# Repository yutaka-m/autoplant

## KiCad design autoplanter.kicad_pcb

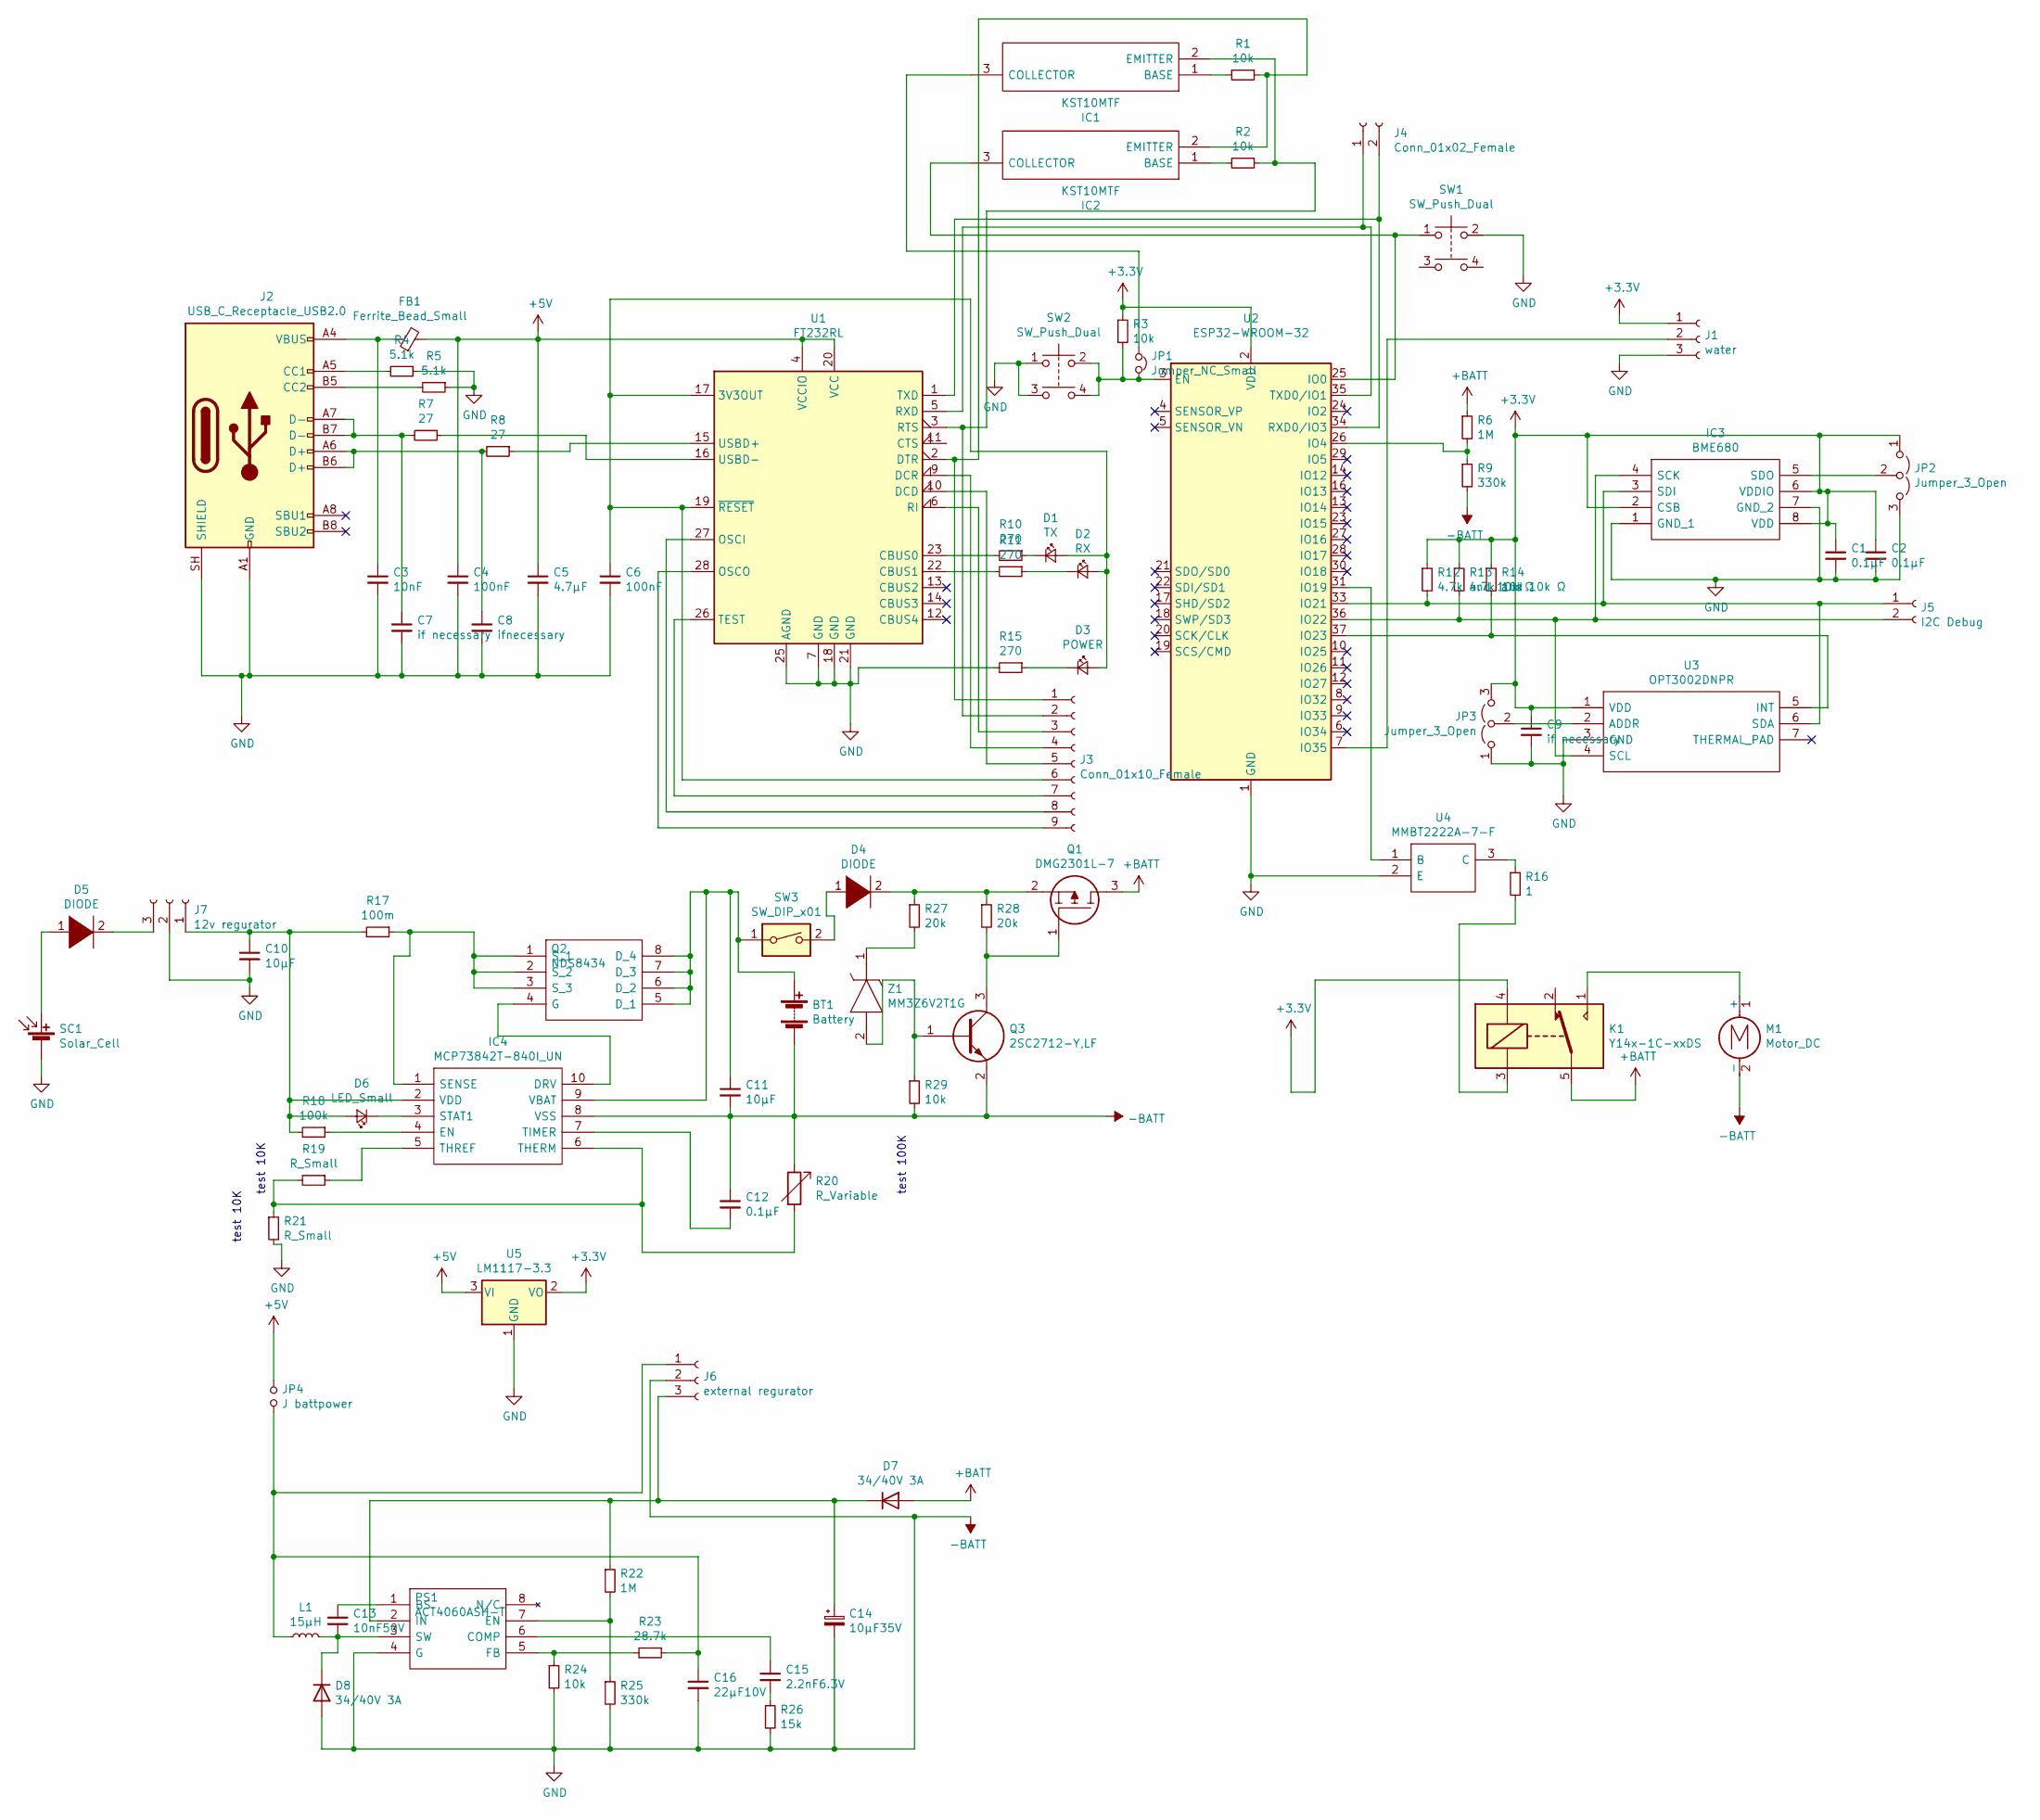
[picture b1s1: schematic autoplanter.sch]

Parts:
BT1: Battery; PinSocket_1x02_P2.54mm_Vertical
C1, C2, C12: 0.1μF; C_1206_3216Metric
C3: 10nF; C_1206_3216Metric
C4, C6: 100nF; C_1206_3216Metric
C5: 4.7μF; C_1206_3216Metric
C7, C9: if necessary; C_1206_3216Metric
C8: ifnecessary; C_1206_3216Metric
C10, C11: 10μF; C_1206_3216Metric
C13: 10nF50V; C_1206_3216Metric
C14: 10μF35V; C_1206_3216Metric
C15: 2.2nF6.3V; C_1206_3216Metric
C16: 22μF10V; C_1206_3216Metric
D1: TX; C_1206_3216Metric
D2: RX; C_1206_3216Metric
D3: POWER; C_1206_3216Metric
D4, D5: DIODE; DIONM7959X282N
D6: LED_Small; C_1206_3216Metric
D7, D8: 34/40V 3A; DIONM7959X282N
FB1: Ferrite_Bead_Small; C_1206_3216Metric
IC1, IC2: KST10MTF; SOT95P240X120-3N; Mouser Part Number 512-KST10MTF
IC3: BME680; Manufacturer_Part_Number BME680; Mouser Part Number 262-BME680
IC4: MCP73842T-840I_UN; SOP50P490X110-10N; Mouser Part Number 579-MCP73842T840I/UN
J1: water; PinHeader_1x03_P2.54mm_Vertical
J2: USB_C_Receptacle_USB2.0; USB-C_Female_E8124-015-01
J3: Conn_01x10_Female; PinSocket_1x09_P2.54mm_Vertical
J4: Conn_01x02_Female; PinSocket_1x02_P2.54mm_Vertical
J5: I2C Debug; PinSocket_1x02_P2.54mm_Vertical
J6: external regurator; PinSocket_1x03_P2.54mm_Vertical
J7: 12v regurator; PinHeader_1x03_P2.54mm_Vertical
JP1: Jumper_NC_Small; SolderJumper-2_P1.3mm_Open_RoundedPad1.0x1.5mm
JP2, JP3: Jumper_3_Open; SolderJumper-3_P1.3mm_Open_RoundedPad1.0x1.5mm_NumberLabels
JP4: J battpower; SolderJumper-2_P1.3mm_Open_RoundedPad1.0x1.5mm
K1: Y14x-1C-xxDS; Relay_SPDT_HsinDa_Y14
L1: 15μH; C_1206_3216Metric
M1: Motor_DC; PinHeader_1x02_P2.54mm_Vertical
PS1: ACT4060ASH-T; SOIC127P605X175-8N; Manufacturer_Part_Number ACT4060ASH-T; Mouser Part Number 107-ACT4060ASH-T
Q1: DMG2301L-7; SOT96P240X110-3N; Mouser Part Number 621-DMG2301L-7
Q2: NDS8434; SOIC127P600X175-8N; Mouser Part Number 512-NDS8434
Q3: 2SC2712-Y,LF; SOT95P260X140-3N; Mouser Part Number 757-2SC2712-YLF
R1, R2, R3, R14, R24, R29: 10k; C_1206_3216Metric
R4, R5: 5.1k; C_1206_3216Metric
R6, R22: 1M; C_1206_3216Metric
R7, R8: 27; C_1206_3216Metric
R9, R25: 330k; C_1206_3216Metric
R10, R11, R15: 270; C_1206_3216Metric
R12, R13: 4.7k and 10k Ω; C_1206_3216Metric
R16: 1; C_1206_3216Metric
R17: 100m; C_1206_3216Metric
R18: 100k; C_1206_3216Metric
R19, R21: R_Small; C_1206_3216Metric
R20: R_Variable; R_1206_3216Metric
R23: 28.7k; C_1206_3216Metric
R26: 15k; C_1206_3216Metric
R27, R28: 20k; C_1206_3216Metric
SC1: Solar_Cell; PinSocket_1x02_P2.54mm_Vertical
SW1, SW2: SW_Push_Dual; SW_PUSH_6mm
SW3: SW_DIP_x01; SW_E-Switch_EG1271_DPDT
U1: FT232RL; SSOP-28_5.3x10.2mm_P0.65mm
U2: ESP32-WROOM-32
U3: OPT3002DNPR; Mouser Part Number 595-OPT3002DNPR
U4: MMBT2222A-7-F; SOT103P240X110-3N; Mouser Part Number 621-MMBT2222A-F
U5: LM1117-3.3; SOT-223
Z1: MM3Z6V2T1G; SOD2512X110N; Mouser Part Number 863-MM3Z6V2T1G

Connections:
+3V3: C1.1, C2.1, C9.1, IC3.2 (CSB), IC3.6 (VDDIO), IC3.8 (VDD), J1.1, JP2.1 (A), JP3.3 (B), K1.4, R3.1, R12.1, R13.1, R14.1, U2.2 (VDD), U3.1 (VDD), U5.2 (VO)
+5V: C4.1, C5.1, FB1.2, JP4.1, U1.4 (VCCIO), U1.20 (VCC), U5.3 (VI)
+BATT: D7.1 (A), K1.5, K1.6, Q1.3, R6.1
-BATT: BT1.2 (-), C1.2, C2.2, C3.2, C4.2, C5.2, C6.2, C7.2, C8.2, C9.2, C10.2, C11.2, C12.1, C14.2, C16.2, D8.1 (A), IC3.1 (GND_1), IC3.7 (GND_2), IC4.8 (VSS), J1.3, J2.A1 (GND), J2.A12 (GND), J2.B1 (GND), J2.B12 (GND), J2.SH (SHIELD), J6.2, J7.2, JP2.3 (B), JP3.1 (A), M1.2 (-), PS1.4 (G), Q3.2, R4.1, R5.1, R9.2, R15.2, R20.1, R21.2, R24.2, R25.2, R26.2, R29.2, SC1.2 (-), SW1.2, SW2.1, SW2.3, U1.7 (GND), U1.18 (GND), U1.21 (GND), U1.25 (AGND), U2.1 (GND), U2.15 (GND), U2.38 (GND), U2.39 (GND), U3.3 (GND), U4.2 (E), U5.1 (GND)
unnamed: BT1.1 (+), C11.1, IC4.9 (VBAT), Q2.5 (D_1), Q2.6 (D_2), Q2.7 (D_3), Q2.8 (D_4), SW3.1
unnamed: C3.1, FB1.1, J2.A4 (VBUS), J2.A9 (VBUS), J2.B4 (VBUS), J2.B9 (VBUS)
unnamed: C6.1, D1.2 (A), D2.2 (A), D3.2 (A), J3.6, U1.17 (3V3OUT), U1.19 (~RESET~)
unnamed: C7.1, J2.A7 (D-), J2.B7 (D-), R7.2
unnamed: C8.1, J2.A6 (D+), J2.B6 (D+), R8.2
unnamed: C10.1, D6.2 (A), IC4.2 (VDD), J7.1, R17.2, R18.2
unnamed: C12.2, IC4.7 (TIMER)
unnamed: C13.1, PS1.1 (BS)
unnamed: C13.2, D8.2 (K), L1.2, PS1.3 (SW)
unnamed: C14.1, D7.2 (K), J6.3, PS1.2 (IN), R22.1
unnamed: C15.1, PS1.6 (COMP)
unnamed: C15.2, R26.1
unnamed: C16.1, J6.1, JP4.2, L1.1, R23.1
unnamed: D1.1 (K), R10.1
unnamed: D2.1 (K), R11.1
unnamed: D3.1 (K), R15.1
unnamed: D4.1 (K), SW3.2
unnamed: D4.2 (A), Q1.2, R27.1, R28.1
unnamed: D5.1 (K), SC1.1 (+)
unnamed: D5.2 (A), J7.3
unnamed: D6.1 (K), IC4.3 (STAT1)
unnamed: IC1.1 (BASE), R1.2
unnamed: IC1.2 (EMITTER), J3.2, R2.1, U1.3 (RTS)
unnamed: IC1.3 (COLLECTOR), JP1.1
unnamed: IC2.1 (BASE), R2.2
unnamed: IC2.2 (EMITTER), J3.1, R1.1, U1.2 (DTR)
unnamed: IC2.3 (COLLECTOR), SW1.1, U2.25 (IO0)
unnamed: IC3.3 (SDI), J5.1, R12.2, U2.33 (IO21), U3.6 (SDA)
unnamed: IC3.4 (SCK), J5.2, R13.2, U2.36 (IO22), U3.4 (SCL)
unnamed: IC3.5 (SDO), JP2.2 (C)
unnamed: IC4.1 (SENSE), Q2.1 (S_1), Q2.2 (S_2), Q2.3 (S_3), R17.1
unnamed: IC4.4 (EN), R18.1
unnamed: IC4.5 (THREF), R19.1
unnamed: IC4.6 (THERM), R19.2, R20.2, R21.1
unnamed: IC4.10 (DRV), Q2.4 (G)
unnamed: J1.2, U2.7 (IO35)
unnamed: J2.A5 (CC1), R4.2
unnamed: J2.B5 (CC2), R5.2
unnamed: J3.3, U1.6 (RI)
unnamed: J3.4, U1.9 (DCR)
unnamed: J3.5, U1.10 (DCD)
unnamed: J3.7, U1.26 (TEST)
unnamed: J3.8, U1.27 (OSCI)
unnamed: J3.9, U1.28 (OSCO)
unnamed: J4.1, U1.5 (RXD), U2.35 (TXD0/IO1)
unnamed: J4.2, U1.1 (TXD), U2.34 (RXD0/IO3)
unnamed: JP1.2, R3.2, SW2.2, SW2.4, U2.3 (EN)
unnamed: JP3.2 (C), U3.2 (ADDR)
unnamed: K1.1, M1.1 (+)
unnamed: K1.3, R16.2
unnamed: PS1.5 (FB), R23.2, R24.1
unnamed: PS1.7 (EN), R22.2, R25.1
unnamed: Q1.1, Q3.3, R28.2
unnamed: Q3.1, R29.1, Z1.2
unnamed: R6.2, R9.1, U2.26 (IO4)
unnamed: R7.1, U1.16 (USBD-)
unnamed: R8.1, U1.15 (USBD+)
unnamed: R10.2, U1.23 (CBUS0)
unnamed: R11.2, U1.22 (CBUS1)
unnamed: R14.2, U2.37 (IO23), U3.5 (INT)
unnamed: R16.1, U4.3 (C)
unnamed: R27.2, Z1.1
unnamed: U2.31 (IO19), U4.1 (B)

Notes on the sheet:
test 100K
test 10K

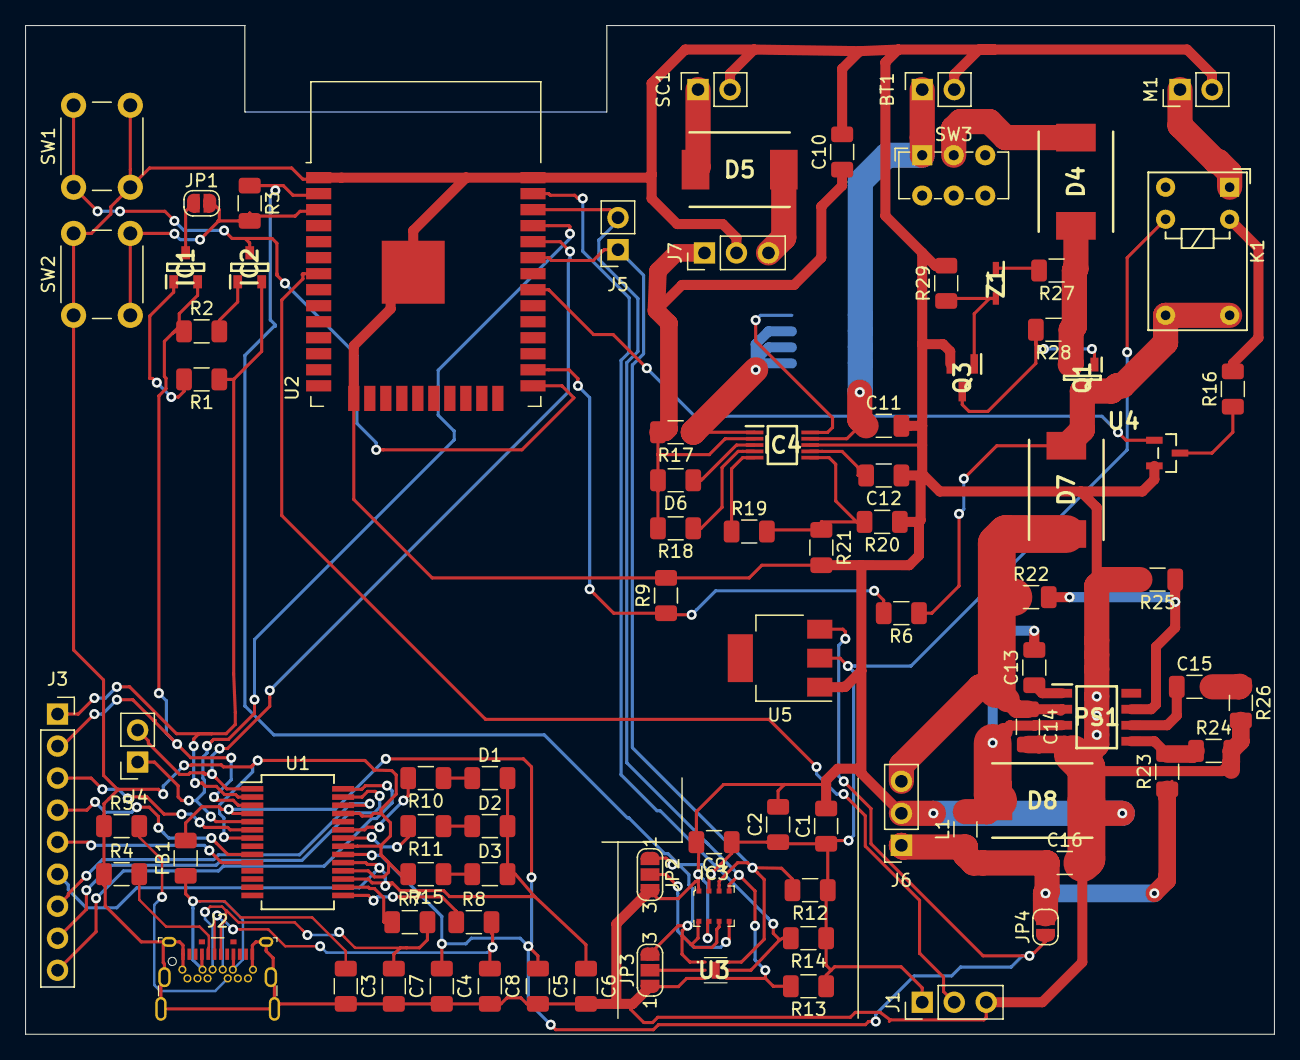
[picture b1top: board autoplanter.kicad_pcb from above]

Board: 2 copper layers, 99.1 x 80.0 mm, 87 parts (1 on the bottom side), 67 nets.

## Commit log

2020-07-23 Fixed regurator and added low voltage safe circuit.
2022-04-11 Add models.
